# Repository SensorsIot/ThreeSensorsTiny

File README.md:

# ThreeSensorsTiny
Three Ultrasonic sensors connected to a ATtiny and connected through I2C

These are the sketches for the YouTube video: https://youtu.be/vj0SUYo8f_A

They might include some errors.

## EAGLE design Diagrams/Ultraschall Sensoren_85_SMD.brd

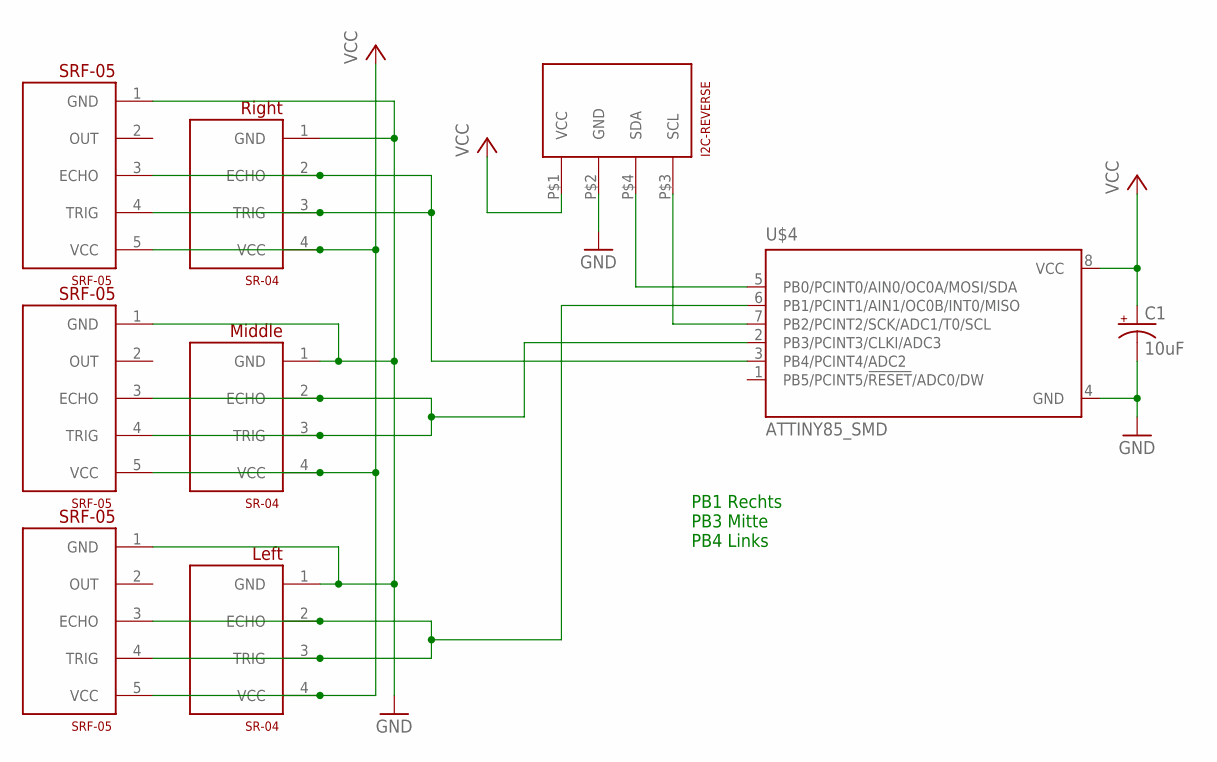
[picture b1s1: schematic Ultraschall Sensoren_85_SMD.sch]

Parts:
C1: 10uF; EIA3216
LINKS: Left; HC-SR04
MIDDLE: Middle; HC-SR04
RIGHT: Right; HC-SR04
U$1, U$3, U$5: SRF-05
U$2: I2C-REVERSE; I2C-CONNECTOR
U$4: ATTINY85_SMD

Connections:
GND: C1.C (-), LINKS.1 (GND), MIDDLE.1 (GND), RIGHT.1 (GND), U$1.1 (GND), U$2.P$2 (GND), U$3.1 (GND), U$4.4 (GND), U$5.1 (GND)
unnamed: RIGHT.2 (ECHO), RIGHT.3 (TRIG), U$1.3 (ECHO), U$1.4 (TRIG), U$4.3 (PB4/PCINT4/ADC2)
unnamed: MIDDLE.2 (ECHO), MIDDLE.3 (TRIG), U$3.3 (ECHO), U$3.4 (TRIG), U$4.2 (PB3/PCINT3/CLKI/ADC3)
unnamed: U$2.P$3 (SCL), U$4.7 (PB2/PCINT2/SCK/ADC1/T0/SCL)
unnamed: U$2.P$4 (SDA), U$4.5 (PB0/PCINT0/AIN0/OC0A/MOSI/SDA)
unnamed: LINKS.2 (ECHO), LINKS.3 (TRIG), U$4.6 (PB1/PCINT1/AIN1/OC0B/INT0/MISO), U$5.3 (ECHO), U$5.4 (TRIG)
VCC: C1.A (+), LINKS.4 (VCC), MIDDLE.4 (VCC), RIGHT.4 (VCC), U$1.5 (VCC), U$2.P$1 (VCC), U$3.5 (VCC), U$4.8 (VCC), U$5.5 (VCC)

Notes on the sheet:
PB1 Rechts PB3 Mitte PB4 Links

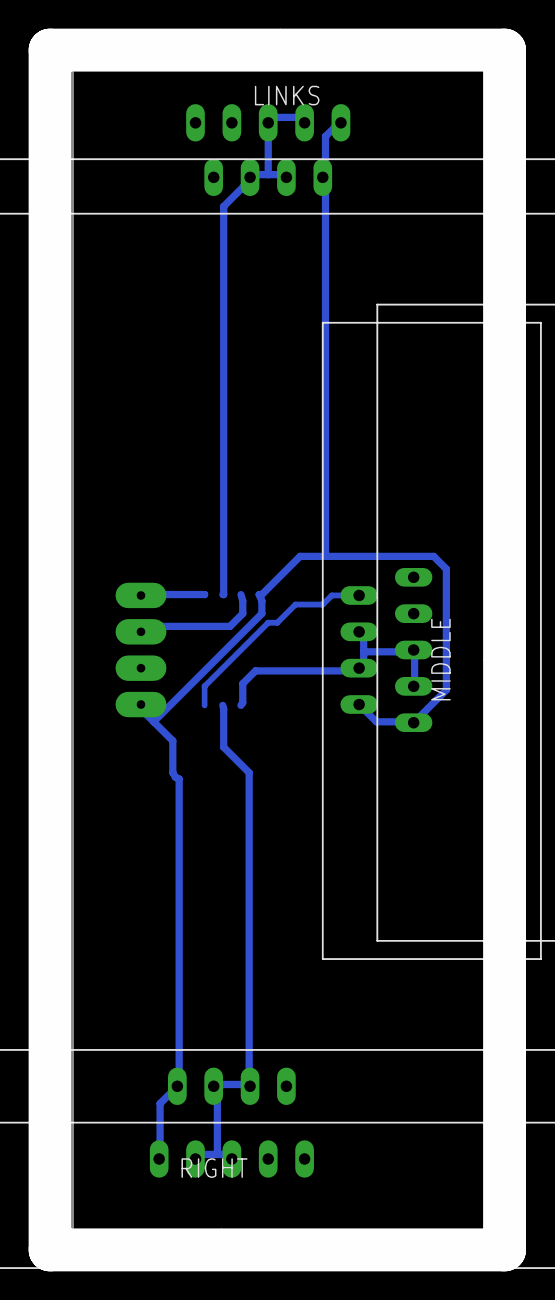
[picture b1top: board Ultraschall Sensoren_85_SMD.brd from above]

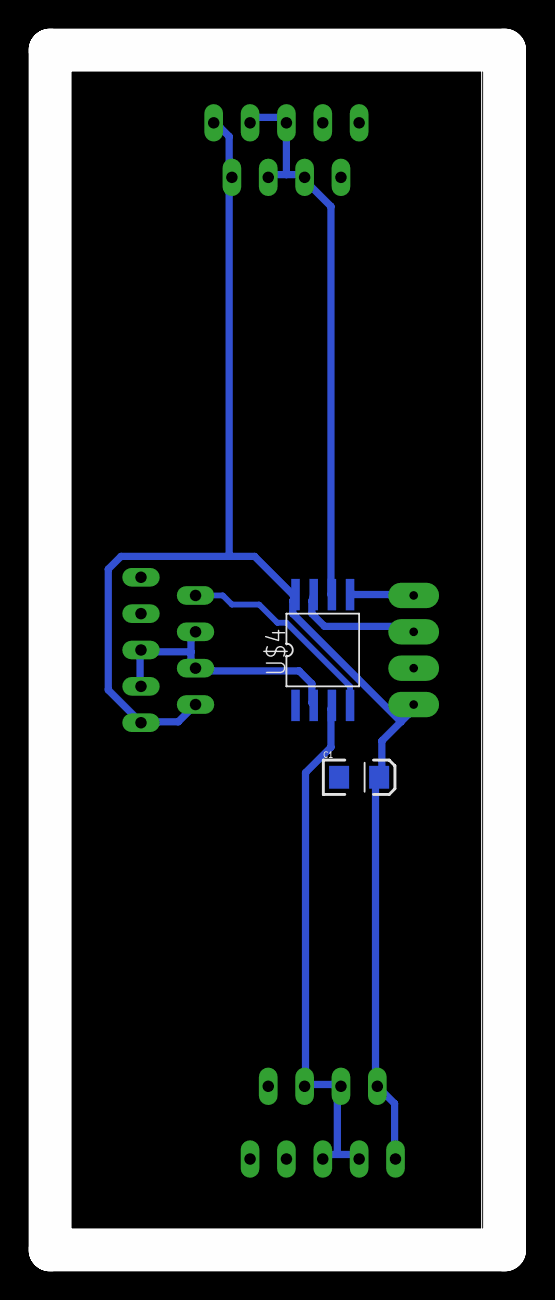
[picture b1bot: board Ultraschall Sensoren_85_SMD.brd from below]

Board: 2 copper layers, 31.8 x 83.8 mm, 9 parts (2 on the bottom side), 7 nets.

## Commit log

2016-07-29 :tada: Added .gitattributes & .gitignore files
2017-03-16 Added diagrams

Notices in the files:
parts and their libraries:
SparkFun-Retired: Licensing:Creative Commons ShareAlike 4.0 International - https://creativecommons.org/licenses/by-sa/4.0
